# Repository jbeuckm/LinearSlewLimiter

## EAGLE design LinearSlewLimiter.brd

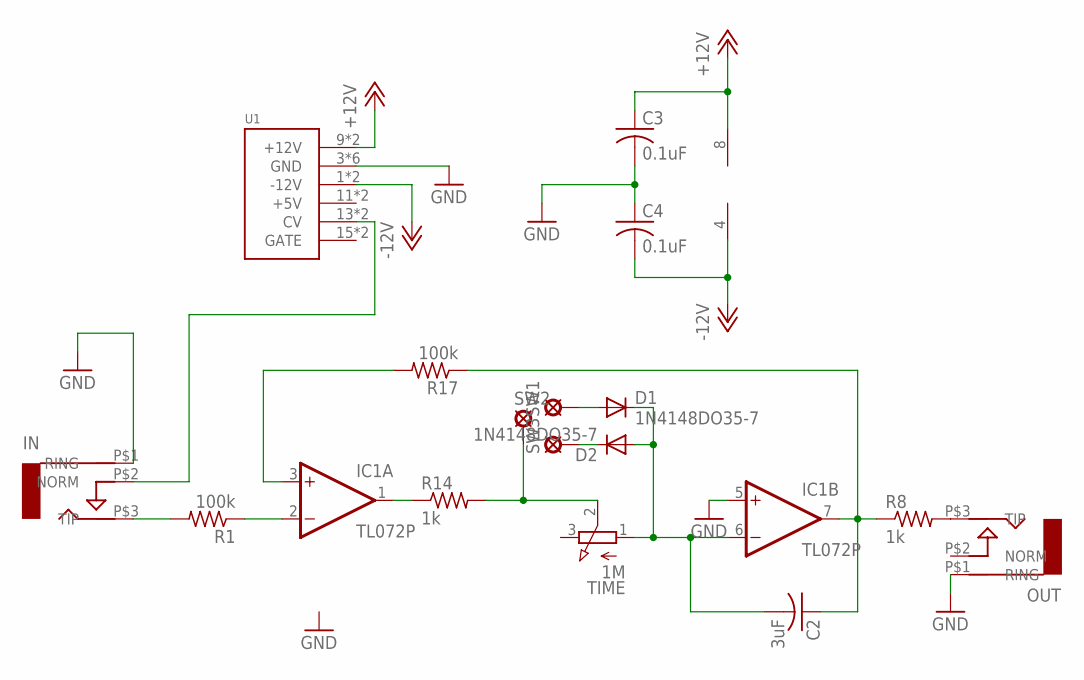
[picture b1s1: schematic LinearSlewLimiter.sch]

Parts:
C2: 3uF; C050-055X075
C3, C4: 0.1uF; C025-030X050
D1, D2: 1N4148DO35-7; DO35-7
IC1: TL072P; DIL08
IN: AUDIO-JACK; ERTHENVAR-JACK-90DEG
OUT: AUDIO-JACK; ERTHENVAR-JACK-90DEG
R1, R17: 100k; 0207/7
R8, R14: 1k; 0207/7
SW1, SW2, SW3: LSP10
TIME: 1M; 3RP/1610N
U1: POWER; POWER_16

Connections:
+12V: C3.1, IC1.8 (V+), U1.9 (+12V), U1.10 (+12V)
-12V: C4.2, IC1.4 (V-), U1.1 (-12V), U1.2 (-12V)
GND: C3.2, C4.1, IC1.5 (+IN), IN.P$1 (RING), OUT.P$1 (RING), U1.3 (GND), U1.4 (GND), U1.5 (GND), U1.6 (GND), U1.7 (GND), U1.8 (GND)
unnamed: IC1.2 (-IN), R1.1
unnamed: C2.1, IC1.7 (OUT), R8.1, R17.1
unnamed: IN.P$3 (TIP), R1.2
unnamed: C2.2, D1.C, D2.A, IC1.6 (-IN), TIME.1 (A)
unnamed: R14.2, SW2.MP, TIME.2 (S)
unnamed: IC1.1 (OUT), R14.1
unnamed: IC1.3 (+IN), R17.2
unnamed: D1.A, SW1.MP
unnamed: D2.C, SW3.MP
unnamed: OUT.P$3 (TIP), R8.2
unnamed: IN.P$2 (NORM), U1.13 (CV), U1.14 (CV)

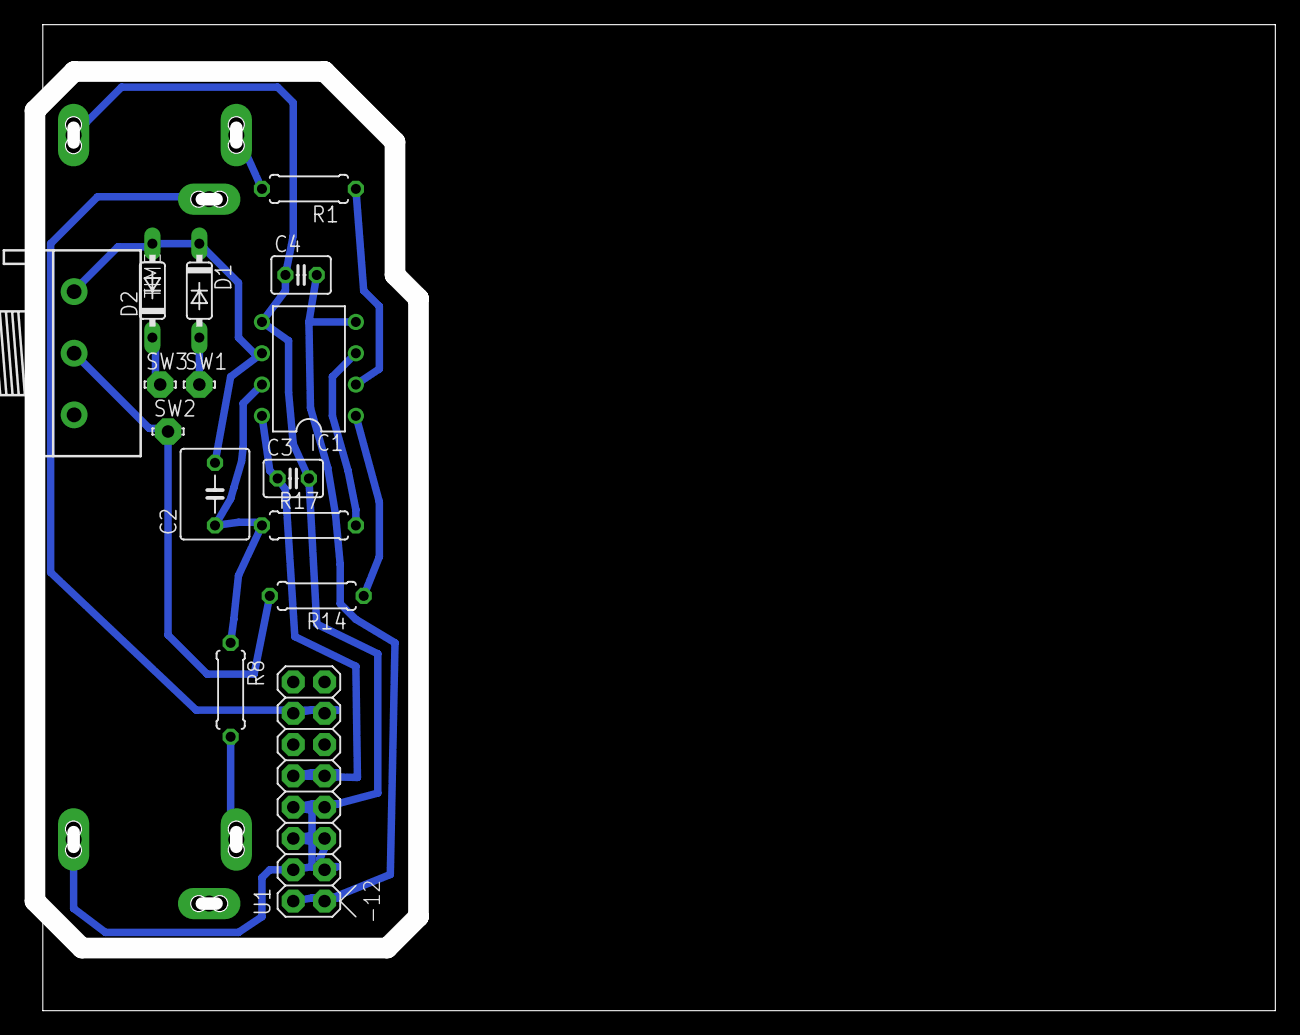
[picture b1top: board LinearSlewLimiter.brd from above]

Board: 2 copper layers, 99.8 x 78.3 mm, 17 parts (0 on the bottom side), 14 nets.

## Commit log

2015-10-10 working board cut
